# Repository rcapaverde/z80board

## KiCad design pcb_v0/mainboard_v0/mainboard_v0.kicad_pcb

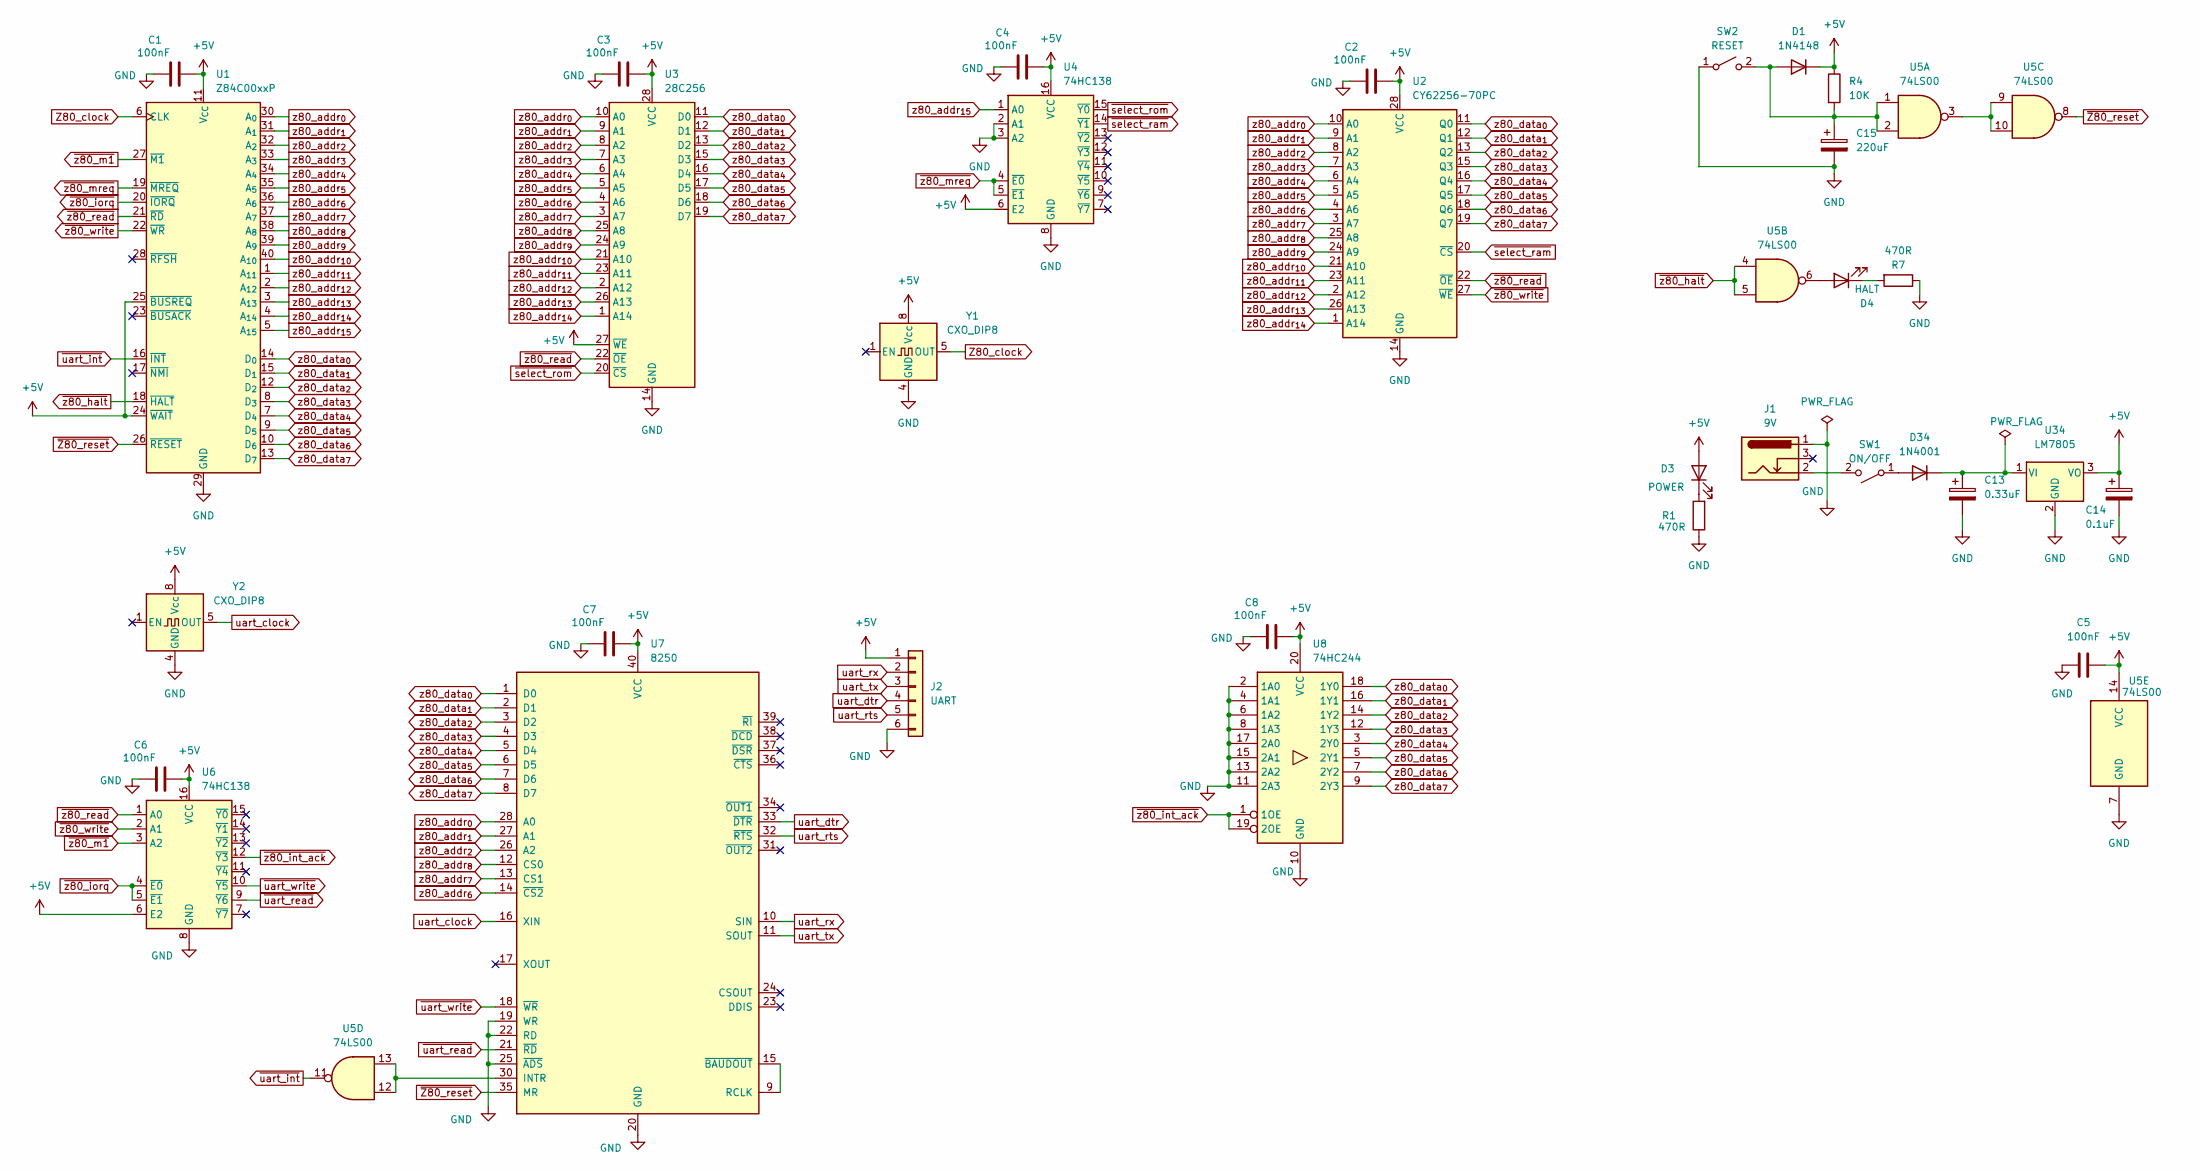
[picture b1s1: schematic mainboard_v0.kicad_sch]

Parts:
C1, C2, C3, C4, C5, C6, C7, C8: 100nF; C_Disc_D5.1mm_W3.2mm_P5.00mm
C13: 0.33uF; CP_Radial_D5.0mm_P2.50mm
C14: 0.1uF; CP_Radial_D5.0mm_P2.50mm
C15: 220uF; C_Disc_D5.1mm_W3.2mm_P5.00mm
D1: 1N4148; D_DO-35_SOD27_P7.62mm_Horizontal
D3: POWER; LED_D5.0mm
D4: HALT; LED_D5.0mm
D34: 1N4001; D_DO-41_SOD81_P10.16mm_Horizontal
J1: 9V; BarrelJack_Horizontal
J2: UART; PinHeader_1x06_P2.54mm_Vertical
R1, R7: 470R; R_Axial_DIN0207_L6.3mm_D2.5mm_P7.62mm_Horizontal
R4: 10K; R_Axial_DIN0207_L6.3mm_D2.5mm_P7.62mm_Horizontal
SW1: ON/OFF; jrx
SW2: RESET; SW_PUSH_6mm
U1: Z84C00xxP; DIP-40_W15.24mm
U2: CY62256-70PC; DIP-28_W15.24mm
U3: 28C256; DIP_Socket-28_W6.9mm_W7.62mm_W10.16mm_W12.7mm_W13.5mm_3M_22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
U4, U6: 74HC138; DIP-16_W7.62mm
U5: 74LS00; DIP-14_W7.62mm
U7: 8250; DIP-40_W15.24mm
U8: 74HC244; DIP-20_W7.62mm
U34: LM7805; TO-220-3_Vertical
Y1, Y2: CXO_DIP8; Oscillator_DIP-8

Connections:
+5V: C1.2, C2.2, C3.2, C4.2, C5.2, C6.2, C7.2, C8.2, C14.1, D1.1 (K), D3.2 (A), J2.1, R4.1, U1.11 (V_{CC}), U1.24 (~WAIT), U1.25 (~BUSREQ), U2.28 (VCC), U3.27 (~WE), U3.28 (VCC), U4.6 (E2), U4.16 (VCC), U5.14 (VCC), U6.6 (E2), U6.16 (VCC), U7.40 (VCC), U8.20 (VCC), U34.3 (VO), Y1.8 (Vcc), Y2.8 (Vcc)
GND: C1.1, C2.1, C3.1, C4.1, C5.1, C6.1, C7.1, C8.1, C13.2, C14.2, C15.2, J1.1, J2.6, R1.1, R7.1, SW2.1 (A), U1.29 (GND), U2.14 (GND), U3.14 (GND), U4.2 (A1), U4.3 (A2), U4.8 (GND), U5.7 (GND), U6.8 (GND), U7.19 (WR), U7.20 (GND), U7.22 (RD), U7.25 (~ADS), U8.2 (1A0), U8.4 (1A1), U8.6 (1A2), U8.8 (1A3), U8.10 (GND), U8.11 (2A3), U8.13 (2A2), U8.15 (2A1), U8.17 (2A0), U34.2 (GND), Y1.4 (GND), Y2.4 (GND)
unnamed: C15.1, D1.2 (A), R4.2, SW2.2 (B), U5.1, U5.2
unnamed: D3.1 (K), R1.2
unnamed: D4.2 (A), U5.6
unnamed: D4.1 (K), R7.2
unnamed: D34.2 (A), SW1.1 (A)
unnamed: C13.1, D34.1 (K), U34.1 (VI)
unnamed: J1.2, SW1.2 (B)
unnamed: U5.3, U5.9, U5.10
unnamed: U5.12, U5.13, U7.30 (INTR)
unnamed: U7.9 (RCLK), U7.15 (~BAUDOUT)
Z80_clock: U1.6 (CLK), Y1.5 (OUT)
uart_clock: U7.16 (XIN), Y2.5 (OUT)
uart_dtr: J2.4, U7.33 (~DTR)
uart_rts: J2.5, U7.32 (~RTS)
uart_rx: J2.2, U7.10 (SIN)
uart_tx: J2.3, U7.11 (SOUT)
z80_addr_{0}: U1.30 (A_{0}), U2.10 (A0), U3.10 (A0), U7.28 (A0)
z80_addr_{1}: U1.31 (A_{1}), U2.9 (A1), U3.9 (A1), U7.27 (A1)
z80_addr_{2}: U1.32 (A_{2}), U2.8 (A2), U3.8 (A2), U7.26 (A2)
z80_addr_{3}: U1.33 (A_{3}), U2.7 (A3), U3.7 (A3)
z80_addr_{4}: U1.34 (A_{4}), U2.6 (A4), U3.6 (A4)
z80_addr_{5}: U1.35 (A_{5}), U2.5 (A5), U3.5 (A5)
z80_addr_{6}: U1.36 (A_{6}), U2.4 (A6), U3.4 (A6), U7.14 (~CS2)
z80_addr_{7}: U1.37 (A_{7}), U2.3 (A7), U3.3 (A7), U7.13 (CS1)
z80_addr_{8}: U1.38 (A_{8}), U2.25 (A8), U3.25 (A8), U7.12 (CS0)
z80_addr_{9}: U1.39 (A_{9}), U2.24 (A9), U3.24 (A9)
z80_addr_{10}: U1.40 (A_{10}), U2.21 (A10), U3.21 (A10)
z80_addr_{11}: U1.1 (A_{11}), U2.23 (A11), U3.23 (A11)
z80_addr_{12}: U1.2 (A_{12}), U2.2 (A12), U3.2 (A12)
z80_addr_{13}: U1.3 (A_{13}), U2.26 (A13), U3.26 (A13)
z80_addr_{14}: U1.4 (A_{14}), U2.1 (A14), U3.1 (A14)
z80_addr_{15}: U1.5 (A_{15}), U4.1 (A0)
z80_data_{0}: U1.14 (D_{0}), U2.11 (Q0), U3.11 (D0), U7.1 (D0), U8.18 (1Y0)
z80_data_{1}: U1.15 (D_{1}), U2.12 (Q1), U3.12 (D1), U7.2 (D1), U8.16 (1Y1)
z80_data_{2}: U1.12 (D_{2}), U2.13 (Q2), U3.13 (D2), U7.3 (D2), U8.14 (1Y2)
z80_data_{3}: U1.8 (D_{3}), U2.15 (Q3), U3.15 (D3), U7.4 (D3), U8.12 (1Y3)
z80_data_{4}: U1.7 (D_{4}), U2.16 (Q4), U3.16 (D4), U7.5 (D4), U8.3 (2Y0)
z80_data_{5}: U1.9 (D_{5}), U2.17 (Q5), U3.17 (D5), U7.6 (D5), U8.5 (2Y1)
z80_data_{6}: U1.10 (D_{6}), U2.18 (Q6), U3.18 (D6), U7.7 (D6), U8.7 (2Y2)
z80_data_{7}: U1.13 (D_{7}), U2.19 (Q7), U3.19 (D7), U7.8 (D7), U8.9 (2Y3)
~Z80_reset: U1.26 (~RESET), U5.8, U7.35 (MR)
~select_ram: U2.20 (~CS), U4.14 (~Y1)
~select_rom: U3.20 (~CS), U4.15 (~Y0)
~uart_int: U1.16 (~INT), U5.11
~uart_read: U6.9 (~Y6), U7.21 (~RD)
~uart_write: U6.10 (~Y5), U7.18 (~WR)
~z80_halt: U1.18 (~HALT), U5.4, U5.5
~z80_int_ack: U6.12 (~Y3), U8.1 (1OE), U8.19 (2OE)
~z80_iorq: U1.20 (~IORQ), U6.4 (~E0), U6.5 (~E1)
~z80_m1: U1.27 (~M1), U6.3 (A2)
~z80_mreq: U1.19 (~MREQ), U4.4 (~E0), U4.5 (~E1)
~z80_read: U1.21 (~RD), U2.22 (~OE), U3.22 (~OE), U6.1 (A0)
~z80_write: U1.22 (~WR), U2.27 (~WE), U6.2 (A1)

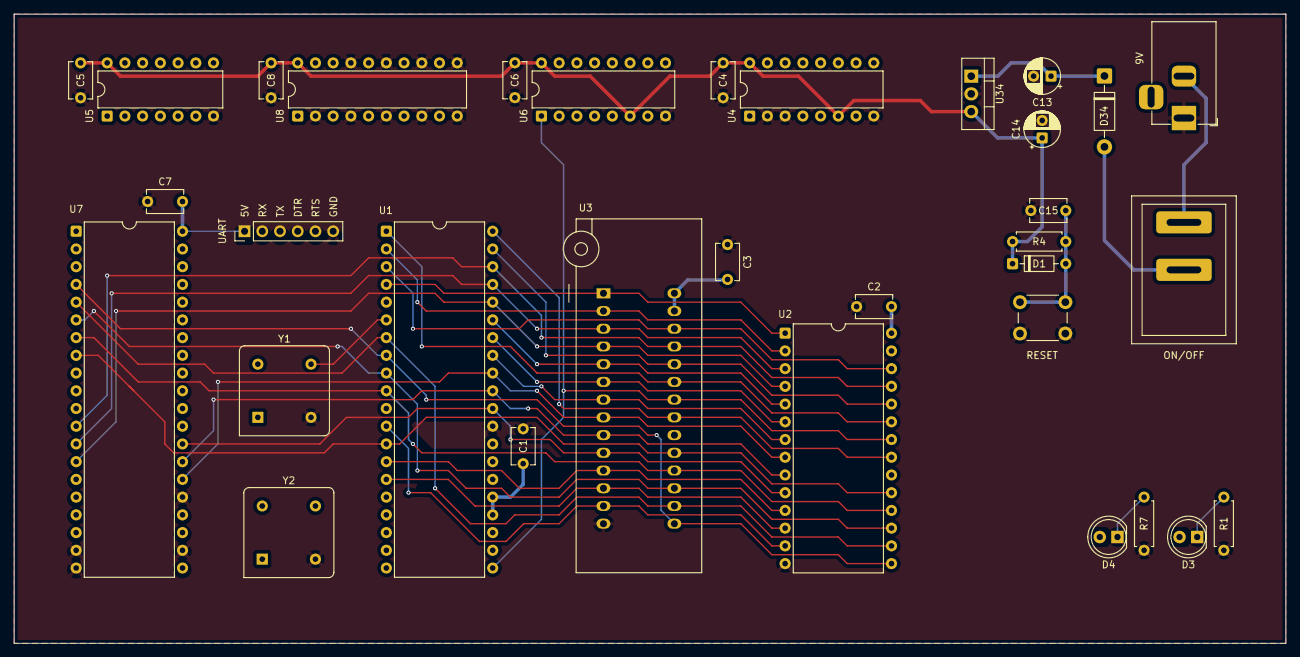
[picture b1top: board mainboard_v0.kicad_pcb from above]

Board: 2 copper layers, 182.2 x 90.2 mm, 33 parts (0 on the bottom side), 55 nets.

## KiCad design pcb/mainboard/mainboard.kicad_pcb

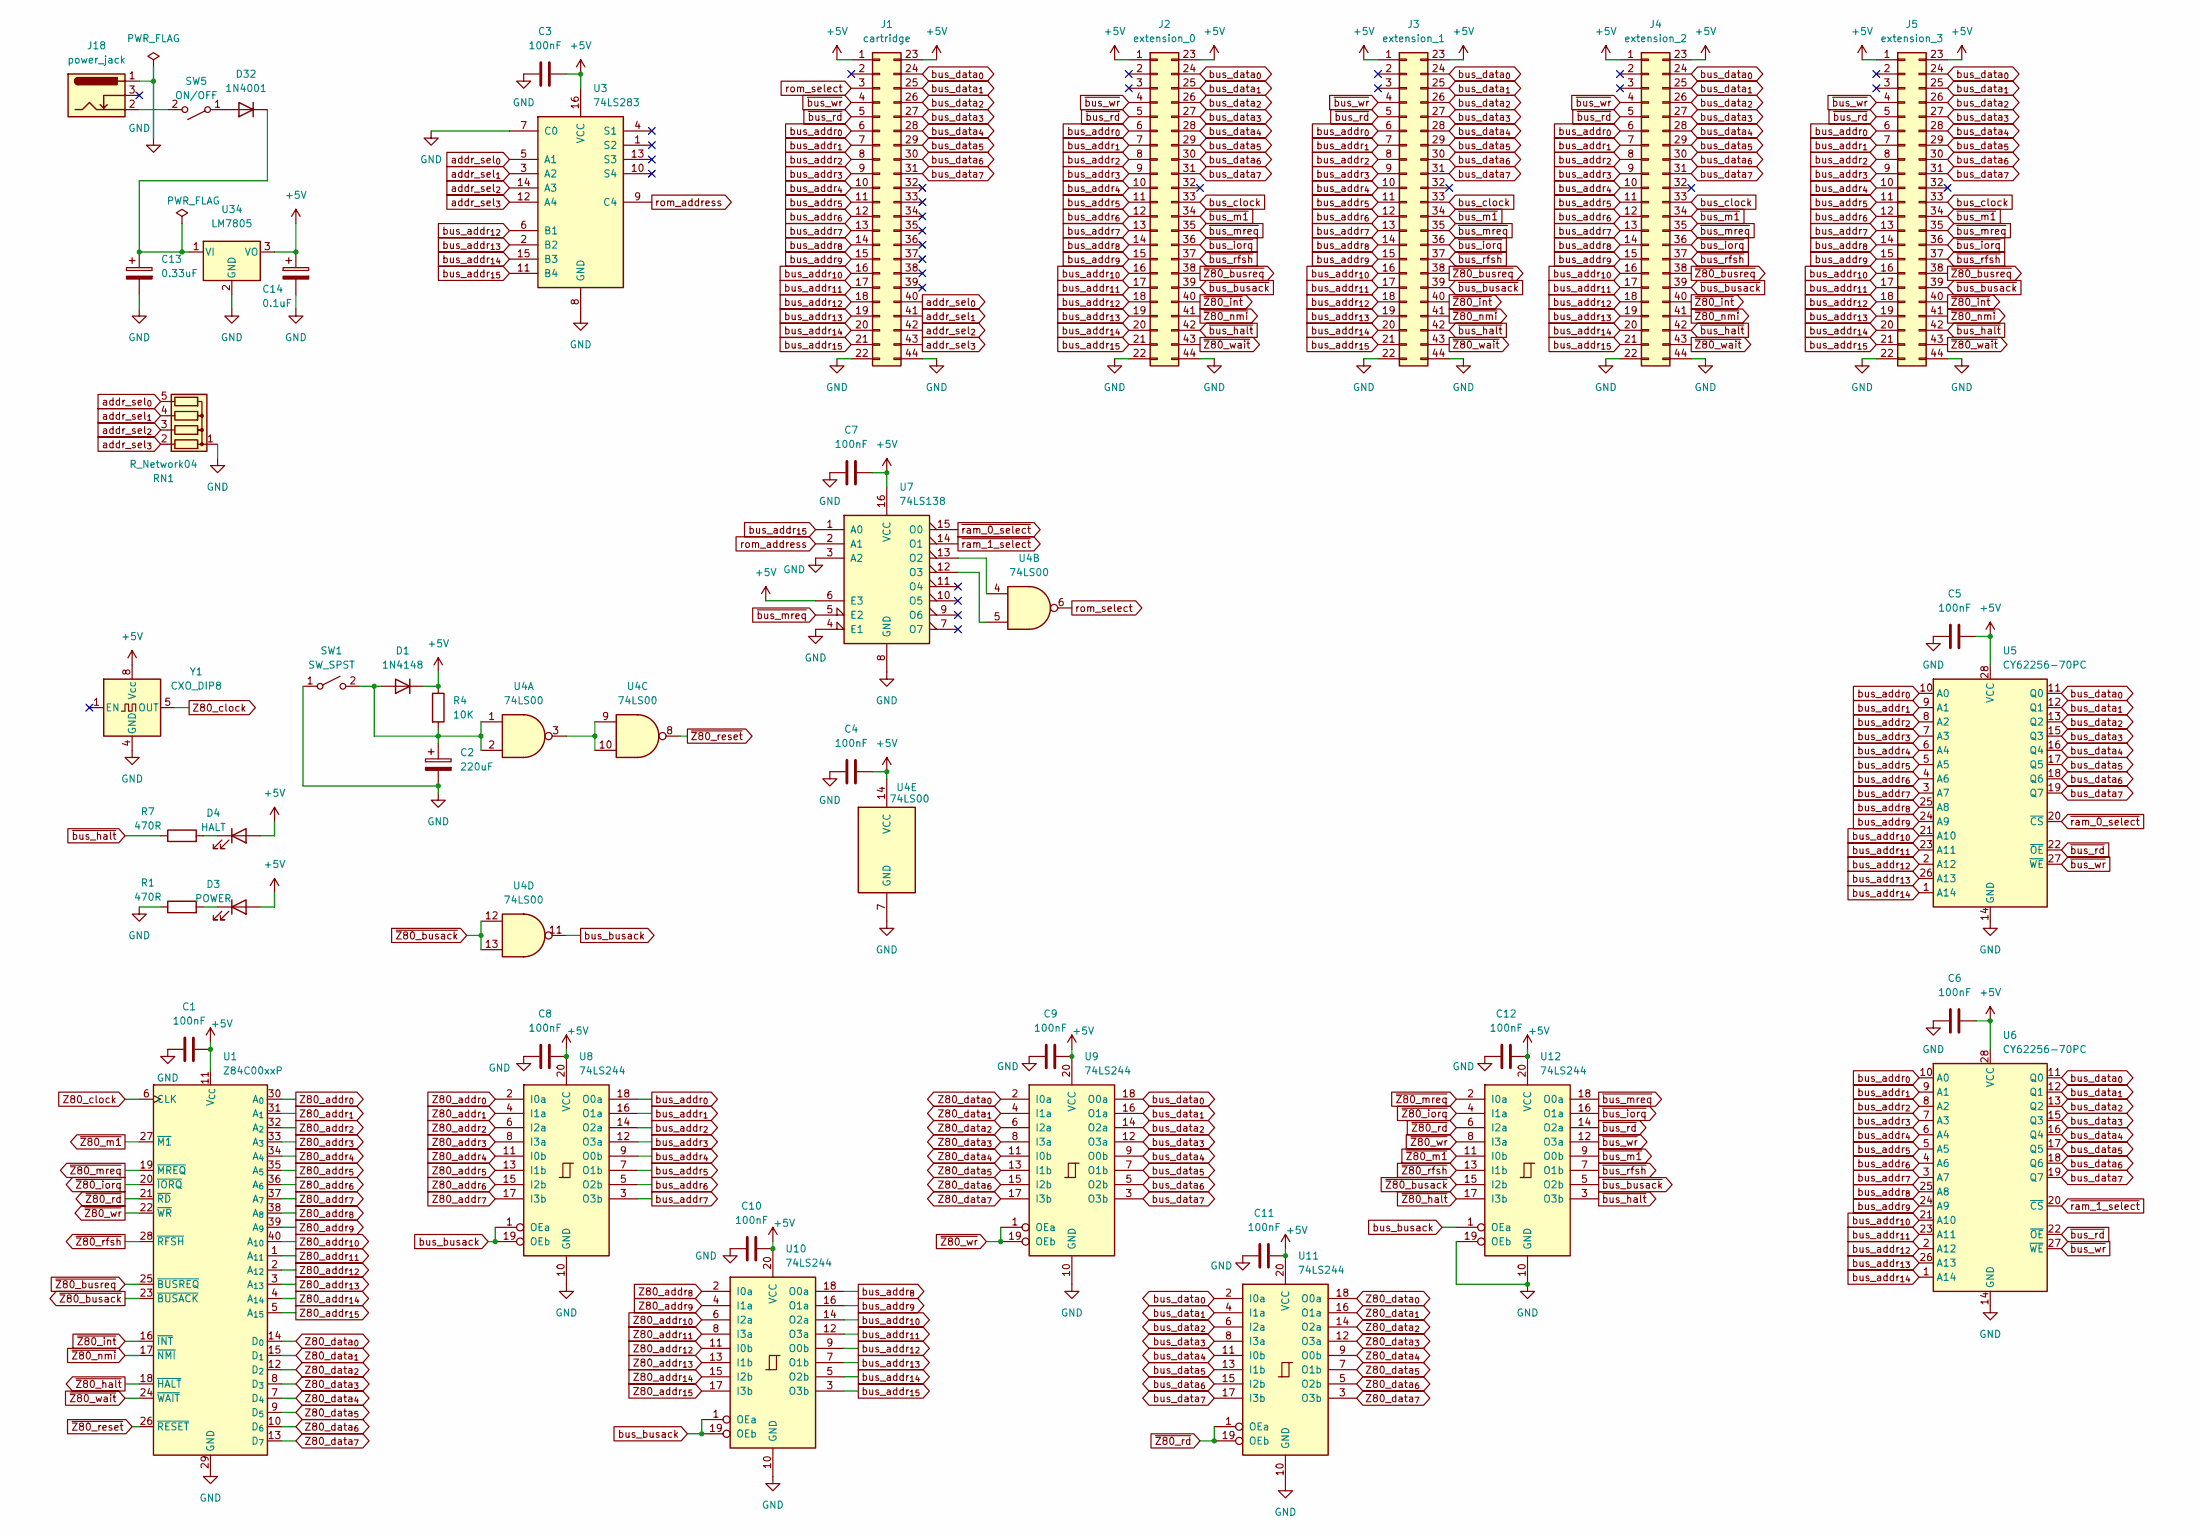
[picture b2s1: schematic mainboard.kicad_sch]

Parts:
C1, C3, C4, C5, C6, C7, C8, C9, C10, C11, C12: 100nF; C_Disc_D5.1mm_W3.2mm_P5.00mm
C2: 220uF; C_Disc_D5.1mm_W3.2mm_P5.00mm
C13: 0.33uF; CP_Radial_D5.0mm_P2.50mm
C14: 0.1uF; CP_Radial_D5.0mm_P2.50mm
D1: 1N4148; D_DO-35_SOD27_P7.62mm_Horizontal
D3: POWER; LED_D5.0mm
D4: HALT; LED_D5.0mm
D32: 1N4001; D_DO-41_SOD81_P10.16mm_Horizontal
J1: cartridge; male-edge-connector-44
J2: extension_0; male-edge-connector-44
J3: extension_1; male-edge-connector-44
J4: extension_2; male-edge-connector-44
J5: extension_3; male-edge-connector-44
J18: power_jack; BarrelJack_Horizontal
R1, R7: 470R; R_Axial_DIN0207_L6.3mm_D2.5mm_P7.62mm_Horizontal
R4: 10K; R_Axial_DIN0207_L6.3mm_D2.5mm_P7.62mm_Horizontal
RN1: R_Network04; R_Array_SIP5
SW1: SW_SPST; SW_PUSH_6mm
SW5: ON/OFF; jrx
U1: Z84C00xxP; DIP-40_W15.24mm
U3: 74LS283; DIP-16_W7.62mm
U4: 74LS00; DIP-14_W7.62mm
U5, U6: CY62256-70PC; DIP-28_W15.24mm
U7: 74LS138; DIP-16_W7.62mm
U8, U9, U10, U11, U12: 74LS244; DIP-20_W7.62mm
U34: LM7805; TO-220-3_Vertical
Y1: CXO_DIP8; Oscillator_DIP-8

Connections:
+5V: C1.2, C3.2, C4.2, C5.2, C6.2, C7.2, C8.2, C9.2, C10.2, C11.2, C12.2, C14.1, D1.1 (K), D3.2 (A), D4.2 (A), J1.1, J1.23, J2.1, J2.23, J3.1, J3.23, J4.1, J4.23, J5.1, J5.23, R4.1, U1.11 (V_{CC}), U3.16 (VCC), U4.14 (VCC), U5.28 (VCC), U6.28 (VCC), U7.6 (E3), U7.16 (VCC), U8.20 (VCC), U9.20 (VCC), U10.20 (VCC), U11.20 (VCC), U12.20 (VCC), U34.3 (VO), Y1.8 (Vcc)
GND: C1.1, C2.2, C3.1, C4.1, C5.1, C6.1, C7.1, C8.1, C9.1, C10.1, C11.1, C12.1, C13.2, C14.2, J1.22, J1.44, J2.22, J2.44, J3.22, J3.44, J4.22, J4.44, J5.22, J5.44, J18.1, R1.1, RN1.1 (common), SW1.1 (A), U1.29 (GND), U3.7 (C0), U3.8 (GND), U4.7 (GND), U5.14 (GND), U6.14 (GND), U7.3 (A2), U7.4 (E1), U7.8 (GND), U8.10 (GND), U9.10 (GND), U10.10 (GND), U11.10 (GND), U12.10 (GND), U12.19 (OEb), U34.2 (GND), Y1.4 (GND)
unnamed: C2.1, D1.2 (A), R4.2, SW1.2 (B), U4.1, U4.2
unnamed: D3.1 (K), R1.2
unnamed: D4.1 (K), R7.2
unnamed: D32.2 (A), SW5.1 (A)
unnamed: C13.1, D32.1 (K), U34.1 (VI)
unnamed: J18.2, SW5.2 (B)
unnamed: U4.3, U4.9, U4.10
unnamed: U4.4, U7.13 (O2)
unnamed: U4.5, U7.12 (O3)
Z80_addr_{0}: U1.30 (A_{0}), U8.2 (I0a)
Z80_addr_{1}: U1.31 (A_{1}), U8.4 (I1a)
Z80_addr_{2}: U1.32 (A_{2}), U8.6 (I2a)
Z80_addr_{3}: U1.33 (A_{3}), U8.8 (I3a)
Z80_addr_{4}: U1.34 (A_{4}), U8.11 (I0b)
Z80_addr_{5}: U1.35 (A_{5}), U8.13 (I1b)
Z80_addr_{6}: U1.36 (A_{6}), U8.15 (I2b)
Z80_addr_{7}: U1.37 (A_{7}), U8.17 (I3b)
Z80_addr_{8}: U1.38 (A_{8}), U10.2 (I0a)
Z80_addr_{9}: U1.39 (A_{9}), U10.4 (I1a)
Z80_addr_{10}: U1.40 (A_{10}), U10.6 (I2a)
Z80_addr_{11}: U1.1 (A_{11}), U10.8 (I3a)
Z80_addr_{12}: U1.2 (A_{12}), U10.11 (I0b)
Z80_addr_{13}: U1.3 (A_{13}), U10.13 (I1b)
Z80_addr_{14}: U1.4 (A_{14}), U10.15 (I2b)
Z80_addr_{15}: U1.5 (A_{15}), U10.17 (I3b)
Z80_clock: U1.6 (CLK), Y1.5 (OUT)
Z80_data_{0}: U1.14 (D_{0}), U9.2 (I0a), U11.18 (O0a)
Z80_data_{1}: U1.15 (D_{1}), U9.4 (I1a), U11.16 (O1a)
Z80_data_{2}: U1.12 (D_{2}), U9.6 (I2a), U11.14 (O2a)
Z80_data_{3}: U1.8 (D_{3}), U9.8 (I3a), U11.12 (O3a)
Z80_data_{4}: U1.7 (D_{4}), U9.11 (I0b), U11.9 (O0b)
Z80_data_{5}: U1.9 (D_{5}), U9.13 (I1b), U11.7 (O1b)
Z80_data_{6}: U1.10 (D_{6}), U9.15 (I2b), U11.5 (O2b)
Z80_data_{7}: U1.13 (D_{7}), U9.17 (I3b), U11.3 (O3b)
addr_sel_{0}: J1.40, RN1.5 (R4), U3.5 (A1)
addr_sel_{1}: J1.41, RN1.4 (R3), U3.3 (A2)
addr_sel_{2}: J1.42, RN1.3 (R2), U3.14 (A3)
addr_sel_{3}: J1.43, RN1.2 (R1), U3.12 (A4)
bus_addr_{0}: J1.6, J2.6, J3.6, J4.6, J5.6, U5.10 (A0), U6.10 (A0), U8.18 (O0a)
bus_addr_{1}: J1.7, J2.7, J3.7, J4.7, J5.7, U5.9 (A1), U6.9 (A1), U8.16 (O1a)
bus_addr_{2}: J1.8, J2.8, J3.8, J4.8, J5.8, U5.8 (A2), U6.8 (A2), U8.14 (O2a)
bus_addr_{3}: J1.9, J2.9, J3.9, J4.9, J5.9, U5.7 (A3), U6.7 (A3), U8.12 (O3a)
bus_addr_{4}: J1.10, J2.10, J3.10, J4.10, J5.10, U5.6 (A4), U6.6 (A4), U8.9 (O0b)
bus_addr_{5}: J1.11, J2.11, J3.11, J4.11, J5.11, U5.5 (A5), U6.5 (A5), U8.7 (O1b)
bus_addr_{6}: J1.12, J2.12, J3.12, J4.12, J5.12, U5.4 (A6), U6.4 (A6), U8.5 (O2b)
bus_addr_{7}: J1.13, J2.13, J3.13, J4.13, J5.13, U5.3 (A7), U6.3 (A7), U8.3 (O3b)
bus_addr_{8}: J1.14, J2.14, J3.14, J4.14, J5.14, U5.25 (A8), U6.25 (A8), U10.18 (O0a)
bus_addr_{9}: J1.15, J2.15, J3.15, J4.15, J5.15, U5.24 (A9), U6.24 (A9), U10.16 (O1a)
bus_addr_{10}: J1.16, J2.16, J3.16, J4.16, J5.16, U5.21 (A10), U6.21 (A10), U10.14 (O2a)
bus_addr_{11}: J1.17, J2.17, J3.17, J4.17, J5.17, U5.23 (A11), U6.23 (A11), U10.12 (O3a)
bus_addr_{12}: J1.18, J2.18, J3.18, J4.18, J5.18, U3.6 (B1), U5.2 (A12), U6.2 (A12), U10.9 (O0b)
bus_addr_{13}: J1.19, J2.19, J3.19, J4.19, J5.19, U3.2 (B2), U5.26 (A13), U6.26 (A13), U10.7 (O1b)
bus_addr_{14}: J1.20, J2.20, J3.20, J4.20, J5.20, U3.15 (B3), U5.1 (A14), U6.1 (A14), U10.5 (O2b)
bus_addr_{15}: J1.21, J2.21, J3.21, J4.21, J5.21, U3.11 (B4), U7.1 (A0), U10.3 (O3b)
bus_clock: J2.33, J3.33, J4.33, J5.33
bus_data_{0}: J1.24, J2.24, J3.24, J4.24, J5.24, U5.11 (Q0), U6.11 (Q0), U9.18 (O0a), U11.2 (I0a)
bus_data_{1}: J1.25, J2.25, J3.25, J4.25, J5.25, U5.12 (Q1), U6.12 (Q1), U9.16 (O1a), U11.4 (I1a)
bus_data_{2}: J1.26, J2.26, J3.26, J4.26, J5.26, U5.13 (Q2), U6.13 (Q2), U9.14 (O2a), U11.6 (I2a)
bus_data_{3}: J1.27, J2.27, J3.27, J4.27, J5.27, U5.15 (Q3), U6.15 (Q3), U9.12 (O3a), U11.8 (I3a)
bus_data_{4}: J1.28, J2.28, J3.28, J4.28, J5.28, U5.16 (Q4), U6.16 (Q4), U9.9 (O0b), U11.11 (I0b)
bus_data_{5}: J1.29, J2.29, J3.29, J4.29, J5.29, U5.17 (Q5), U6.17 (Q5), U9.7 (O1b), U11.13 (I1b)
bus_data_{6}: J1.30, J2.30, J3.30, J4.30, J5.30, U5.18 (Q6), U6.18 (Q6), U9.5 (O2b), U11.15 (I2b)
bus_data_{7}: J1.31, J2.31, J3.31, J4.31, J5.31, U5.19 (Q7), U6.19 (Q7), U9.3 (O3b), U11.17 (I3b)
rom_address: U3.9 (C4), U7.2 (A1)
rom_select: J1.3, U4.6
~Z80_busack: U1.23 (~BUSACK), U4.12, U4.13, U12.15 (I2b)
~Z80_busreq: J2.38, J3.38, J4.38, J5.38, U1.25 (~BUSREQ)
~Z80_halt: U1.18 (~HALT), U12.17 (I3b)
~Z80_int: J2.40, J3.40, J4.40, J5.40, U1.16 (~INT)
~Z80_iorq: U1.20 (~IORQ), U12.4 (I1a)
~Z80_m1: U1.27 (~M1), U12.11 (I0b)
~Z80_mreq: U1.19 (~MREQ), U12.2 (I0a)
~Z80_nmi: J2.41, J3.41, J4.41, J5.41, U1.17 (~NMI)
~Z80_reset: U1.26 (~RESET), U4.8
~Z80_rfsh: U1.28 (~RFSH), U12.13 (I1b)
~Z80_wait: J2.43, J3.43, J4.43, J5.43, U1.24 (~WAIT)
~bus_busack: J2.39, J3.39, J4.39, J5.39, U12.5 (O2b)
~bus_halt: J2.42, J3.42, J4.42, J5.42, R7.1, U12.3 (O3b)
~bus_iorq: J2.36, J3.36, J4.36, J5.36, U12.16 (O1a)
~bus_m1: J2.34, J3.34, J4.34, J5.34, U12.9 (O0b)
~bus_mreq: J2.35, J3.35, J4.35, J5.35, U7.5 (E2), U12.18 (O0a)
~bus_rd: J1.5, J2.5, J3.5, J4.5, J5.5, U5.22 (~OE), U6.22 (~OE), U12.14 (O2a)
~bus_rfsh: J2.37, J3.37, J4.37, J5.37, U12.7 (O1b)
~bus_wr: J1.4, J2.4, J3.4, J4.4, J5.4, U5.27 (~WE), U6.27 (~WE), U12.12 (O3a)
~ram_0_select: U5.20 (~CS), U7.15 (O0)
~ram_1_select: U6.20 (~CS), U7.14 (O1)

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
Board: 2 copper layers, 42 parts (0 on the bottom side), 91 nets, no tracks yet.
